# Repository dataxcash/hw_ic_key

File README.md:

# hw_ic_key — KEY Secure Key Vault (B1 Security Module)

<p align="center">

</p>

<p align="center"><em>Current hardware revision — 8-layer, 32.00 × 73.40 mm PCB (TOP / BOTTOM)</em></p>

Open-source hardware — KiCad design files for the **KEY module**, the secure
key vault that gates the IOCONVERT V2.0 conversion card family. It carries
the hardware root of trust and issues the pre-authentication handshake before
any data path is enabled.

## Status

| Item | Value |
|---|---|
| PCB | 8 layers, 32.00 × 73.40 mm |
| Routing | 0 unrouted nets, DRC 0 violations (0 errors / 0 warnings, refilled) |
| Fabrication data | Gerber (14 layers), Excellon drill, CPL, BOM — `fab/release_r5_u0_73p4mm/` |
| Design files | KiCad 10 (`key_v2.kicad_pro`, `key_v2.kicad_pcb`, `sch/`) |
| Release tag | `r5-u0-73p4mm-release-20261110` |

## Overview

KEY is a B1 security module that connects to the K1 master gate card over
USB Type-C. It holds the hardware vault, flash storage, and the SE050 secure
element that performs mutual authentication with the gatekeeper MCU. Only
after successful pre-authentication is the PCIe data path allowed to start.

```
KEY (B1 security module)
├─ B1 hardware vault + eMMC flash
├─ SE050 secure element (pre-auth / mutual auth over SBU I2C)
├─ M.2 M-key socket
├─ FUSB302 USB-C controller
└─ Type-C link → K1 Master Gate Card
```

## Key Features

- **Secure element**: NXP SE050 (hardware root of trust, key storage)
- **Storage**: eMMC (BGA-153) + LPDDR4 (200-FBGA) memory subsystem
- **Compute**: SOM module (B1 platform) with PMIC + 100 MHz XO
- **Connectivity**: USB Type-C receptacle, M.2 M-key socket
- **Debug**: UART debug header

## Repository Contents

| Path | Description |
|---|---|
| `key_v2.kicad_pro` | KiCad 10 project |
| `key_v2.kicad_pcb` | PCB layout (current revision) |
| `sch/` | Schematics: root, main, power, gate |
| `lib/key_v2_symbols.kicad_sym` | Symbol library — required for schematics |
| `lib/footprint/` | Footprint library (17 custom footprints) |
| `fab/key_v2_bom.csv` | Bill of materials |
| `fab/release_r5_u0_73p4mm/` | Fabrication package: Gerber, drill, CPL, BOM, `MANIFEST.md` |
| `boards/` | Configuration (YAML) |
| `docs/img/` | 3D renders used above |

## Getting Started

1. Install [KiCad](https://www.kicad.org/) 10.x
2. Clone this repository
3. Open `key_v2.kicad_pro`
4. If symbols/footprints show as missing, add `lib/key_v2_symbols.kicad_sym`
   to the symbol library table and `lib/footprint/` to the footprint library
   table (global or project-level)

## Fabrication

`fab/release_r5_u0_73p4mm/MANIFEST.md` lists every file with its SHA-256 and size.
Board stackup is 8-layer; blind/buried vias are used, so check with your
fabricator before ordering.

## License

AGPL-3.0 (see `LICENSE`)

---

*Part of the IOCONVERT V2.0 family: [hw_ic_k1](https://github.com/dataxcash/hw_ic_k1) (master gate card) · [hw_ic_k2](https://github.com/dataxcash/hw_ic_k2) (worker data-plane card)*

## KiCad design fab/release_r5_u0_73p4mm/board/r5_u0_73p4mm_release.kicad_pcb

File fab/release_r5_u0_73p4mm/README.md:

# r5_u0_73p4mm_release — key_v2 终板发布包

- 日期：2026-11-10
- 终板：`board/r5_u0_73p4mm_release.kicad_pcb`
- 终板 sha256：`4ad679b8064b4ae505174c1d6a5d15cc32a3e507ddbfa3cf3c37d8326b3f808d`
- DRC：0 violations / 0 unconnected（`drc.json`）
- 板框：标称 32.000 × 73.400 mm；含 Edge.Cuts 弧鼓实测 32.100 × 73.500 mm
- 层数：8；fill parity：15 zones / mismatch 0
- 关键长度：USB2_DP 91.2910 mm / 36 段 / 7 孔（dL vs DM +4.5368）；PCIE_TC_TX0_N 98.7043 mm；REFCLK_100M_P/N 40.3098 mm / dL 0
- 验收：verify key_v2 7/7 PASS；connectivity split_nets 0；3V3_AUX/U6 收口完成
- U2 首件门槛：连续 >1.5 A 或峰值 >2.5 A / >2 ms / >2% duty ⇒ 下一版 TPS22965DSGR

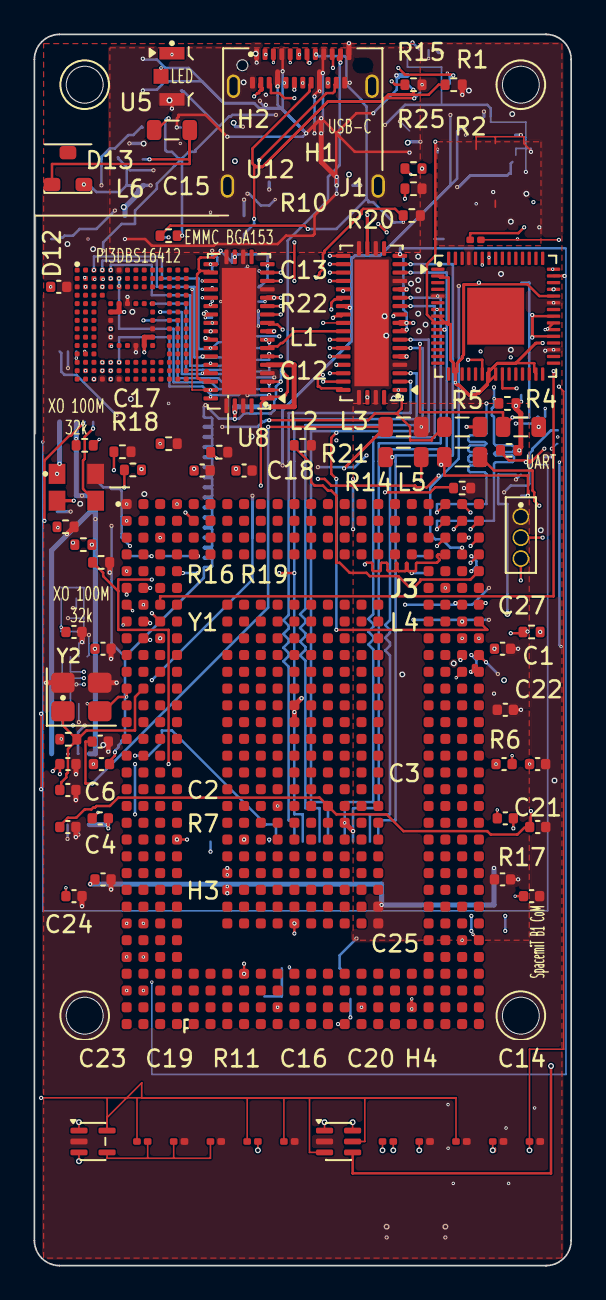
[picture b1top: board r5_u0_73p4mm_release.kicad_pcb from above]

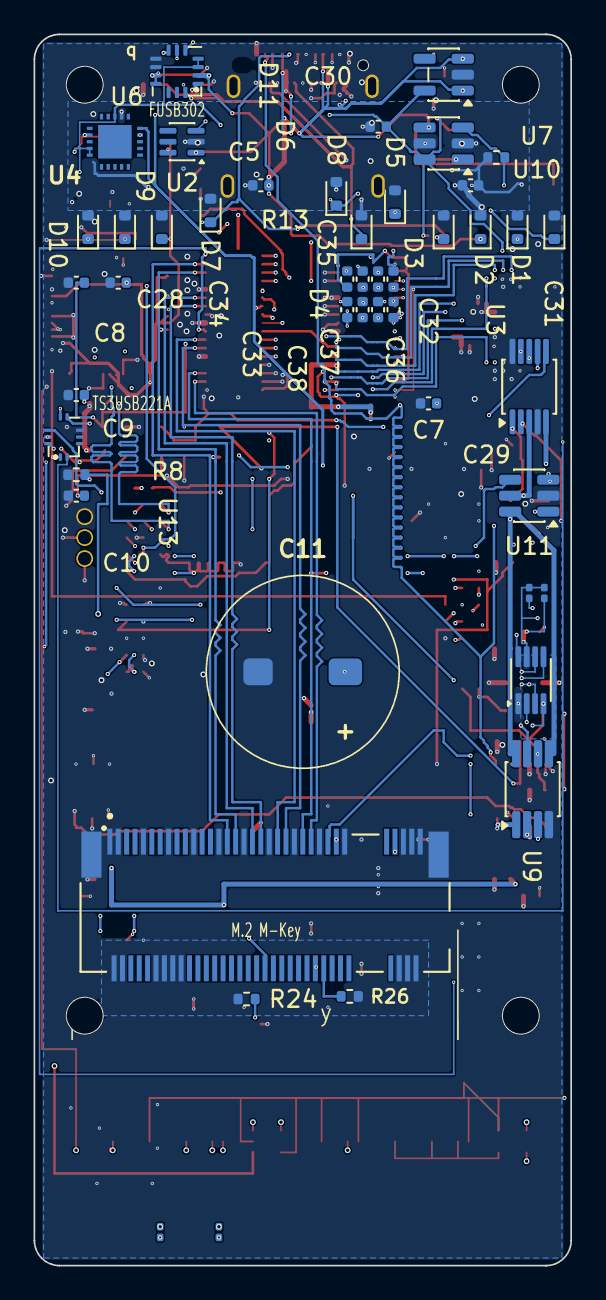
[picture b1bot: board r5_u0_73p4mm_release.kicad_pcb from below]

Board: 8 copper layers, 32.0 x 73.4 mm, 122 parts (47 on the bottom side), 126 nets.

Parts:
C1, C2, C3, C4, C5, C6, C7, C8, C9, C10, C12, C15, C17, C19, C21, C26, C27, C28, C31, C32, C33, C34, C35, C36, C37, C38: 100nF; C_0402_1005Metric
C11: SUPERCAP_1F; KR_5R5V105_SMD_DNI
C13, C14, C16, C18, C20, C22, C29, C30: 10uF; C_0402_1005Metric
C23, C25: 12pF; C_0402_1005Metric
C24: 1uF; C_0402_1005Metric
C39: 10nF; C_0201_0603Metric
C40, C41, C42, C43: 100nF; C_0201_0603Metric
D1, D2, D3, D4, D5, D6, D7, D8, D9, D10, D11: TVS; D_SOD-523
D12: LED; LED_LiteOn_LTST-S326
D13: BAT54C; D_SOT-23
H1, H2, H3, H4: M2.2_NPTH; MountingHole_2.2mm_M2_SmallCrtYd
J1: USB-C; USB_C_Receptacle_Amphenol_12401610E4-2A
J2: M.2 M-Key; M2_M_SOCKET_2230_ONLY
J3: UART; PinHeader_1x03_P1.25mm_Vertical
L1, L2, L3, L4, L5: 1uH; L_0805_2012Metric
L6: 4.7uH; L_0805_2012Metric
R1, R2: 5.1K; R_0402_1005Metric
R3, R8, R10, R11, R15, R16, R17, R18, R20, R21, R22, R23, R26: 10K; R_0402_1005Metric
R4, R19: 100K; R_0402_1005Metric
R5, R6: 4.7K; R_0402_1005Metric
R7: 1M; R_0402_1005Metric
R9, R12: 4.7K; R_0201_0603Metric
R13, R24, R25: 100k; R_0402_1005Metric
R14: 11k; R_0402_1005Metric
R27: 1k; R_0201_0603Metric
R28, R29, R30, R32: 100k; R_0201_0603Metric
R31: 10k; R_0201_0603Metric
R33, R34: 2.2K; R_0201_0603Metric
U1: RP2350 QFN60; QFN-60-1EP_7x7mm_P0.4mm_EP3.4x3.4mm
U2: TPS22919; SOT-363_SC-70-6
U3: CLK_BUF_1TO2; MSOP-10_3x3mm_P0.5mm
U4: SE050C2; HX2QFN20_3x3mm_P0.4mm
U5: EMMC BGA153; EMMC_BGA153
U6: FUSB302
U7: DCDC_12V_3V3; SOT-23-6
U8, U14: PI3DBS16412
U9: SN74LVC2T45; VSSOP-8_3x3mm_P0.65mm
U10: LDO_5V_3V3; SOT-23-5
U11: SN74LVC1T45; SOT-23-6
U12: SpacemiT B1 CoM; B1_PsP_568
U13: TS3USB221A
U15: TLV7011; SOT-353_SC-70-5
U16: SN74LVC1G175; SOT-363_SC-70-6
U17: PCA9306; VSSOP-8_2.3x2mm_P0.5mm
Y1: XO 100M 32k; Crystal_SMD_3225-4Pin_3.2x2.5mm
Y2: XO 100M 32k; XO_3225

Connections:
3V3_AUX: C30.1, C42.1, C43.1, L6.1, R9.2, R12.2, R17.2, R18.2, R29.1, R31.1, U4.11, U4.12, U4.18, U6.3, U6.4, U7.6, U10.5, U13.10, U15.5, U16.3, U16.5, U17.7
AVDD06_DDR: C21.1, C22.1, L5.2, U12.W13
AVDD11_DDR: C19.1, C20.1, L4.2, U12.W10
CC1: D5.1, J1.A5, R1.1, U6.10, U6.11
CC2: D6.1, J1.B5, R2.1, U6.1, U6.14
D_P_SENSE: R27.2, R28.1, U15.3
EMMC_CLK: U5.M6, U12.A20
EMMC_CMD: U5.M5, U12.D22
EMMC_DAT0: U5.A3, U12.C22
EMMC_DAT1: U5.A4, U12.C20
EMMC_DAT2: U5.A5, U12.B22
EMMC_DAT3: U5.B2, U12.D21
EMMC_DAT4: U5.B3, U12.D20
EMMC_DAT5: U5.B4, U12.C21
EMMC_DAT6: U5.B5, U12.B21
EMMC_DAT7: U5.B6, U12.B20
EMMC_DS: U5.H5, U12.A21
EMMC_RST: R11.1, U5.K5
EMMC_VDDI: C24.1, U5.C2
FB_PREAUTH: R13.1, R14.1, U7.3
FUSB_INT#: U6.5, U12.H3
GND: C5.2, C6.2, C7.2, C8.2, C9.2, C10.2, C11.2, C12.2, C13.2, C14.2, C15.2, C16.2, C17.2, C18.2, C19.2, C20.2, C21.2, C22.2, C23.2, C24.2, C25.2, C26.2, C27.2, C28.2, C29.2, C30.2, C39.2, C40.2, C41.2, C42.2, C43.2, D1.2, D2.2, D3.2, D4.2, D5.2, D6.2, D7.2, D8.2, D9.2, D10.2, D11.2, D12.3, J1.A1, J1.A12, J1.B1, J1.B12, J1.SH, J2.1, J2.3, J2.9, J2.15, J2.21, J2.27, J2.33, J2.39, J2.45, J2.51, J2.57, J2.71, J2.73, J2.75, J2.S1, J2.S2, J3.1, R1.2, R2.2, R8.2, R10.2, R14.2, R15.2, R16.2, R20.2, R21.2, R22.2, R23.2, R25.2, R28.2, R30.2, U1.5, U1.33, U1.40, U1.57, U2.2, U3.4, U3.10, U4.19, U5.A6, U5.C4, U5.E7, U5.G5, U5.H10, U5.J5, U5.K8, U5.N2, U5.N5, U5.P4, U5.P6, U6.8, U6.9, U7.2, U8.4, U8.14, U8.19, U8.21, U8.39, U8.41, U8.CP, U9.4, U10.2, U11.2, U12.A1, U13.5, U14.4, U14.14, U14.19, U14.21, U14.39, U14.41, U14.CP, U15.2, U16.2, U17.1, Y1.3, Y1.4, Y2.2
I2C2_SCL: R9.1, U4.10, U6.6, U13.8, U17.6
I2C2_SCL_B1: R33.1, U12.J2, U17.3
I2C2_SDA: R12.1, U4.9, U6.7, U13.7, U17.5
I2C2_SDA_B1: R34.1, U12.J3, U17.4
I2C8_SCL: R5.1, U1.45, U12.F2
I2C8_SDA: R6.1, U1.44, U12.F1
JTAG_SEL: R23.1, U12.A4
LX_BUCK3: C7.1, L2.1, U1.7
LX_BUCK4: C8.1, L3.1, U1.10
LX_BUCK5: C9.1, L4.1, U1.24
LX_BUCK6: C10.1, L5.1, U1.21
LX_BUCK12: C6.1, L1.1, U1.35, U1.38
LX_PREAUTH: D13.1, L6.2, U7.1
M2_3V3: J2.2, J2.4, J2.12, J2.14, J2.16, J2.18, J2.70, J2.72, J2.74, R24.2, R26.2
M2_CLKREQ#: J2.52, R26.1
M2_DEVSLP: J2.38, R25.1
M2_PEDET: J2.69, R24.1
M2_RX0_N: J2.41, U14.7
M2_RX0_P: J2.43, U14.6
M2_RX1_N: J2.29, U14.16
M2_RX1_P: J2.31, U14.15
M2_TX0_N: J2.47, U14.3
M2_TX0_P: J2.49, U14.2
M2_TX1_N: J2.35, U14.12
M2_TX1_P: J2.37, U14.11
MUX_PD: U12.H2, U14.1, U14.10
MUX_SEL: U12.H1, U14.8, U14.17
ORI_PD: U8.1, U8.10, U9.6
ORI_PD_B1: U9.3, U12.B1
ORI_SEL: U8.8, U8.17, U9.7
ORI_SEL_B1: U9.2, U12.C3
PCIEC_RX0_N: U12.K22, U14.37
PCIEC_RX0_P: U12.K21, U14.38
PCIEC_RX1_N: U12.J22, U14.28
PCIEC_RX1_P: U12.J21, U14.29
PCIEC_TX0_N: U12.H22, U14.35
PCIEC_TX0_P: U12.H21, U14.36
PCIEC_TX1_N: U12.G22, U14.26
PCIEC_TX1_P: U12.G21, U14.27
PCIE_R0NB: C4.2, U12.AF2
PCIE_R0PB: C3.2, U12.AF1
PCIE_S1_RX0_N: U8.7, U14.31
PCIE_S1_RX0_P: U8.6, U14.32
PCIE_S1_RX1_N: U8.16, U14.22
PCIE_S1_RX1_P: U8.15, U14.23
PCIE_S1_TX0_N: U8.3, U14.33
PCIE_S1_TX0_P: U8.2, U14.34
PCIE_S1_TX1_N: U8.12, U14.24
PCIE_S1_TX1_P: U8.11, U14.25
PCIE_S2_RX0_N: C38.1, U8.22, U8.35
PCIE_S2_RX0_P: C34.1, U8.23, U8.36
PCIE_S2_RX1_N: C35.1, U8.26, U8.31
PCIE_S2_RX1_P: C31.1, U8.27, U8.32
PCIE_S2_TX0_N: C36.1, U8.24, U8.37
PCIE_S2_TX0_P: C32.1, U8.25, U8.38
PCIE_S2_TX1_N: C37.1, U8.28, U8.33
PCIE_S2_TX1_P: C33.1, U8.29, U8.34
PCIE_T0NB: C2.1, U12.AH2
PCIE_T0PB: C1.1, U12.AH1
PCIE_TC_RX0_N: C4.1, C38.2, D9.1, J1.A3
PCIE_TC_RX0_P: C3.1, C34.2, D10.1, J1.A2
PCIE_TC_RX1_N: C35.2, J1.B2
PCIE_TC_RX1_P: C31.2, J1.B3
PCIE_TC_TX0_N: C2.2, C36.2, D2.1, J1.A11
PCIE_TC_TX0_P: C1.2, C32.2, D1.1, J1.A10
PCIE_TC_TX1_N: C37.2, J1.B10
PCIE_TC_TX1_P: C33.2, J1.B11
PERST#_B1: U11.3, U12.B5
PERST#_SSD: J2.50, R10.1, U11.4
PMIC_INT: R3.1, U1.54, U12.G2
PMIC_SLEEP: U1.42, U12.G3
PWR_5V_PREAUTH: C29.1, D13.3, R13.2, U7.5
PWR_5V_WORK: C11.1, C28.1, U1.2, U1.8, U1.9, U1.17, U1.22, U1.23, U1.29, U1.36, U1.37, U1.41, U2.6
PWR_EN: R8.1, U2.3, U16.4
PWR_EN_CLK: C41.1, R32.2, U16.1
PWR_EN_CLR: C39.1, R31.2, U16.6
PWR_EN_REF: C40.1, R29.2, R30.1, U15.4
PWR_EN_SET_N: R32.1, U15.1
REFCLK_100M_N: C27.1, J2.53, U3.7
REFCLK_100M_P: J2.55, U3.6
REFCLK_B1_N: U3.9, U12.L22
REFCLK_B1_P: U3.8, U12.L21
REFCLK_XO: U3.1, Y2.3
REFCLK_XO_N: C26.1, U3.2
RESET: R4.1, U1.55, U12.G1
SBU1_DET: R19.1, U12.AG21
SBU_EN: R16.1, U12.AM14, U13.6
SBU_I2C_SCL: D7.1, J1.A8, R17.1, U13.1
SBU_I2C_SDA: D8.1, J1.B8, R18.1, U13.2
SBU_SEL: R15.1, U12.AL18, U13.9
STATUS_LED: D12.1, D12.2, U12.AG22
STRAP2: R20.1, U12.F20
STRAP3: R21.1, U12.E22
STRAP4: R22.1, U12.E1
UART0_RX: J3.3, U12.AL15
UART0_TX: J3.2, U12.AL10
USB2_DM: D4.1, J1.A7, J1.B7, U12.AK2
USB2_DP: D11.1, J1.A6, J1.B6, R27.1, U12.AK1
VBUS_IN: C5.1, D3.1, J1.A4, J1.A9, J1.B4, J1.B9, U2.1, U6.2, U7.4, U10.1, U10.3
VDD_0V9: C12.1, C13.1, C14.1, L1.2, U12.AE16, U12.AF16
VDD_1V8: C15.1, C16.1, L2.2, R3.2, R4.2, R5.2, R6.2, R33.2, R34.2, U5.C6, U5.M4, U5.N4, U5.P3, U5.P5, U9.1, U11.1, U12.AA8, U12.AC7, U12.AD7, U12.N11, U12.P11, U12.Y14, U17.2, U17.8
VDD_3V3: C17.1, C18.1, L3.2, R11.2, R19.2, U3.3, U3.5, U4.14, U5.E6, U5.F5, U5.J10, U5.K9, U8.5, U8.9, U8.13, U8.20, U8.30, U8.40, U9.5, U9.8, U11.5, U11.6, U12.AA4, U12.AF11, U12.AJ8, U14.5, U14.9, U14.13, U14.20, U14.30, U14.40, Y2.1, Y2.4
XTAL_24M_XI: C23.1, R7.2, U12.M2, Y1.1
XTAL_24M_XO: C25.1, R7.1, U12.M1, Y1.2

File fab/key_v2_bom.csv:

Ref,Qty,Value,Footprint,Suggested_MPN,MPN_Note,DNP
"C1,C2,C3,C4,C5,C6,C7,C8,C9,C10,C12,C15,C17,C19,C21,C26,C27,C28,C31,C32,C33,C34,C35,C36,C37,C38",26,100nF,Capacitor_SMD:C_0402_1005Metric,LCSC C110251 / FH 0402B104K500NT,"50V X7R, LCSC verified",
C11,1,SUPERCAP_1F,KeyV2_Footprints:KR_5R5V105_SMD_DNI,KR-5R5V105 (DNP),DNI/DNP; vendor PN from value,Y
"C13,C14,C16,C18,C20,C22,C29,C30",8,10uF,Capacitor_SMD:C_0402_1005Metric,LCSC C15525 / Samsung CL05A106MQ5NUNC,"6.3V X5R, LCSC verified",
"C23,C25",2,12pF,Capacitor_SMD:C_0402_1005Metric,LCSC C1547 / FH 0402CG120J500NT,"50V C0G, LCSC verified",
C24,1,1uF,Capacitor_SMD:C_0402_1005Metric,LCSC C52923 / Samsung CL05A105KA5NQNC,"25V X5R, LCSC verified",
"D1,D2,D3,D4,D5,D6,D7,D8,D9,D10,D11",11,TVS,Diode_SMD:D_SOD-523,待定,BOM 未给工作电压/电容/极性，无法唯一选型,
D12,1,LED_DUAL,LED_SMD:LED_LiteOn_LTST-S326,LiteOn LTST-S326KGJRKT,from footprint descr,
D13,1,BAT54C,Diode_SMD:D_SOT-23,BAT54C,generic PN,
J1,1,USB_C_RECEPT_IND,Connector_USB:USB_C_Receptacle_Amphenol_12401610E4-2A,Amphenol 12401610E4-2A,from footprint name,
J2,1,M2_M_SOCKET_2230_ONLY,KeyV2_Footprints:M2_M_SOCKET_2230_ONLY,MTSSD03-67MSW337,from 3D model,
J3,1,UART_DEBUG,KeyV2_Footprints:PinHeader_1x03_P1.25mm_Vertical,待定,仅 1x03 1.25mm 排针，未给安装方向/镀层/品牌,
"L1,L2,L3,L4,L5",5,1uH,Inductor_SMD:L_0805_2012Metric,待定,未给额定电流/饱和电流/直流电阻,
L6,1,4.7uH,Inductor_SMD:L_0805_2012Metric,待定,未给额定电流/饱和电流/直流电阻,
"R1,R2",2,5.1K,Resistor_SMD:R_0402_1005Metric,LCSC C25905 / UNI-ROYAL 0402WGF5101TCE,"1% 0402, LCSC verified",
"R3,R8,R10,R11,R15,R16,R17,R18,R20,R21,R22,R23",12,10K,Resistor_SMD:R_0402_1005Metric,LCSC C25744 / UNI-ROYAL 0402WGF1002TCE,"1% 0402, LCSC verified",
"R4,R19",2,100K,Resistor_SMD:R_0402_1005Metric,LCSC C25741 / UNI-ROYAL 0402WGF1003TCE,"1% 0402, LCSC verified",
"R5,R6,R9,R12",4,4.7K,Resistor_SMD:R_0402_1005Metric,LCSC C25900 / UNI-ROYAL 0402WGF4701TCE,"1% 0402, LCSC verified",
R7,1,1M,Resistor_SMD:R_0402_1005Metric,LCSC C26083 / UNI-ROYAL 0402WGF1004TCE,"1% 0402, LCSC verified",
"R13,R24,R25",3,100k,Resistor_SMD:R_0402_1005Metric,LCSC C25741 / UNI-ROYAL 0402WGF1003TCE,"1% 0402, LCSC verified",
R14,1,11k,Resistor_SMD:R_0402_1005Metric,LCSC C25749 / UNI-ROYAL 0402WGF1102TCE,"1% 0402, LCSC verified",
U1,1,PMIC_P1,Package_DFN_QFN:QFN-60-1EP_7x7mm_P0.4mm_EP3.4x3.4mm,SpacemiT SPM8821,from footprint descr,
U2,1,TPS22919,Package_TO_SOT_SMD:SOT-363_SC-70-6,TI TPS22919DCKR,value+package,
U3,1,CLK_BUF_1TO2,Package_SO:MSOP-10_3x3mm_P0.5mm,待定,仅功能描述，无厂商/型号,
U4,1,SE050C2,KeyV2_Footprints:HX2QFN20_3x3mm_P0.4mm,NXP SE050C2,value; LCSC not verified,
U5,1,EMMC_16G,KeyV2_Footprints:EMMC_BGA153,待定,仅容量/封装，无厂商/料号,
U6,1,FUSB302,KeyV2_Footprints:FUSB302,ON Semi FUSB302MPX,from footprint descr,
U7,1,DCDC_12V_3V3,Package_TO_SOT_SMD:SOT-23-6,待定,仅功能描述，无厂商/型号,
"U8,U14",2,PI3DBS16412,KeyV2_Footprints:PI3DBS16412,Diodes PI3DBS16412,value,
U9,1,SN74LVC2T45,Package_SO:VSSOP-8_3x3mm_P0.65mm,TI SN74LVC2T45DCUR,value+package,
U10,1,LDO_5V_3V3,Package_TO_SOT_SMD:SOT-23-5,待定,仅功能描述，无厂商/型号,
U11,1,SN74LVC1T45,Package_TO_SOT_SMD:SOT-23-6,TI SN74LVC1T45DBVR,value+package,
U12,1,SOM_B1,KeyV2_Footprints:B1_PsP_568,SpacemiT B1,module value,
U13,1,TS3USB221A,KeyV2_Footprints:TS3USB221A,TI TS3USB221ARSER,value+package,
Y1,1,24MHz_9pF,Crystal:Crystal_SMD_3225-4Pin_3.2x2.5mm,待定,未给稳定性/负载电容/品牌,
Y2,1,XO_100M,KeyV2_Footprints:XO_3225,待定,未给输出类型/稳定性/品牌,
